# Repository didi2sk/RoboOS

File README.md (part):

# RoboOS

**English** | [Slovensky](README.sk.md)

A mini operating system for the Raspberry Pi that runs directly on the hardware, no Linux.
You control it with a **USB keyboard** or over a serial line (UART). Output goes to
HDMI and UART at the same time, and both inputs work together.

Current version: **0.150**

## Supported boards

One `kernel8.img` runs on every board with the 64-bit BCM2837 chip; the board is
detected at boot (shown under the logo and in the prompt, e.g. `robo@zero2`).

| Board | Notes |
|-------|-------|
| Raspberry Pi 3 Model B / B+ / A+ | tested on 3B |
| Raspberry Pi Zero 2 W | mini-HDMI; keyboard through an **OTG adapter** on the port marked `USB` (power goes to `PWR IN`); hot-plug works on that port too, with or without a USB hub |
| Raspberry Pi 2 Model B **v1.2** | v1.2 has the BCM2837 (printed on the board: "Raspberry Pi 2 Model B V1.2") |
| Compute Module 3 / 3+ | |

Not supported: Pi 1, Zero / Zero W, Pi 2 v1.1 (32-bit chips), Pi 4 and Pi 5 (different
peripherals, USB behind PCIe).

The ACT LED is on the firmware GPIO expander (3B, CM3), GPIO29 (3B+, 3A+, Zero 2 W - active low)
or GPIO47 (Pi 2 v1.2).

## Putting it on an SD card

1. Format the SD card as **FAT32** with an **MBR** partition table (any size).
2. Copy the whole contents of the `sd/` folder onto it:
   `bootcode.bin`, `start.elf`, `fixup.dat`, `config.txt`, `kernel8.img`,
   plus the folders `APPS` (example programs), `RUN` (autostart) and `FIRMWARE` (WiFi chip firmware).
3. Put the card in the Raspberry Pi and power it on.

## GPIO header (pinout)

*Picture: [Raspberry Pi documentation](https://www.raspberrypi.com/documentation/computers/raspberry-pi.html), © Raspberry Pi Ltd, [CC BY-SA 4.0](https://creativecommons.org/licenses/by-sa/4.0/).*
Odd pins (1, 3, ... 39) = the inner row, even pins (2, 4, ... 40) = the row at the board's edge. The numbers in
RoboOS commands are always **GPIO numbers**, not header pins.

What RoboOS uses by default:

| GPIO (header pin) | used for |
|---|---|
| 2, 3 (3, 5) | I2C: sensors, displays, RTC, FM radio, I2C keypad |
| 14, 15 (8, 10) | UART console (USB-TTL adapter) |
| 8-11 (24, 21, 19, 23) | SPI: RC522 card reader, Waveshare OLED HAT |
| 4 (7) | 1-Wire on the IoT shield (no driver yet) |
| 17, 27, 22, 5 (11, 13, 15, 29) | IoT shield inputs IN1-IN4 = alarm zones (`alarm shield`) |
| 24, 25, 12, 16 (18, 22, 32, 36) | IoT shield outputs / relays (24 = alarm siren) |
| 23 (16) | IoT shield LED (alarm LED) |
| 6 (31) | doorbell button (THT shield) |
| 11, GND, 0, 5, 6, 13, 19, 26 (23-37 inner row) | 4x4 keypad pushed straight on (`alarm keypad plug`) |
| 18, 19 (12, 35) | sound on the Zero 2 W (the Pi 3 uses its jack) |

## Programs and autostart

The SD card is also RoboOS's disk (FAT32 or FAT16, read and write).
RoboOS has its own SD driver (the firmware only loads `kernel8.img` and then steps aside).
If the card is not found, `sd init` shows which step failed and the controller registers.
Since 0.28 the card runs on the SDHOST controller (as in Linux), so that the second controller
(Arasan) is free for WiFi later; if SDHOST does not work, RoboOS uses the Arasan as before and the
boot screen shows a yellow `SDHOST:` line with the reason. `sd` shows which one is used,
`sd init sdhost` / `sd init emmc` try one of them.

- Everything in **`/RUN`** (`*.bin` and `*.bas`) starts automatically after boot,
  in alphabetical order. Press any key within 2 s to skip the autostart.
- `run <name>` starts a program from the current directory, `/RUN` or `/APPS`; the extension
  is optional.
- Moving around the card: `cd APPS`, `cd ..`, `cd /`, `pwd`; the prompt shows where you are
  (`robo@rpi3:/APPS$`). All commands and BASIC (`LOAD`, `SAVE`, `DIR`) take paths relative
  to the current directory. **Tab** completes file and directory names.
- `mkdir <dir>` makes a directory (8.3 name), `rm <file>` deletes a file, `rm <dir>` an empty
  directory. The firmware and kernel files in `/` are protected: deleting them needs `rm -f`.
- **Ctrl+C** stops a running program and returns to the shell.

### BASIC - write programs directly on the RPi

```
robo@rpi3:~$ basic
] 10 PINMODE 17, OUT
] 20 GPIO 17, HIGH : WAIT 500
] 30 GPIO 17, LOW : WAIT 500
] 40 GOTO 20
] RUN                      (Ctrl+C stops it)
] SAVE "/RUN/blink"        (saved as /RUN/blink.bas -> starts after every boot)
] BYE
```

- Commands: `RUN`, `LIST [a-b]`, `NEW`, `SAVE "name"`, `LOAD "name"`, `DIR [path]`, `HELP`, `BYE`;
  `MKDIR "dir"`, `RMDIR "dir"`, `KILL "file"` work in programs too.
  Typing a line number alone deletes that line.
- Statements: `PRINT`/`?`, `INPUT`, `LET`, `IF..THEN..ELSE`, `GOTO`, `GOSUB`/`RETURN`,
  `FOR..TO..STEP`/`NEXT`, `DIM`, `END`, `REM`/`'`, `CLS`, `RANDOMIZE`; separate statements with `:`.
- GPIO: `PINMODE pin, OUT|IN|PULLUP|PULLDOWN`, `GPIO pin, HIGH|LOW`, `GPIO(pin)`, `LED ON|OFF`, `WAIT ms`.
- Pictures: `IMAGE "file", x, y [, w, h]` (see the pictures section).
- Video: `VIDEO "file.mpg"` (see the video section).
- Sound: `SOUND Hz, ms`, `PLAY "notes"`, `VOLUME 0-100`, `PLAYWAV "file.wav"` (see the sound section).
- Network: `NETSEND`, `NETOK`, `NETAVAIL`, `NETRECV`; TCP/UDP: `TCPCONNECT`, `TCPLISTEN`,
  `TCPACCEPT`, `UDPOPEN`, `SOCKPRINT`, `UDPSEND`, `SOCKAVAIL`, `SOCKGET`, `SOCKNUM`, `SOCKCLOSE`
  (see the network sections).
- Functions: `ABS()`, `RND(n)`, `MIN(a,b)`, `MAX(a,b)`, `MILLIS`, `MICROS`, `INKEY`, `TEMP`, `CHR$()` (in PRINT).
- Integers only (64-bit). Keywords must be separated by spaces. `.bas` files are plain text,
  so you can also write them on a PC.
- File names when saving: 8.3 (max 8 characters + extension).

Examples on the card: `APPS/blink.bas`, `APPS/button.bas`, `APPS/knight.bas`,
`APPS/ledsrv.bas` (LED controlled over TCP), `APPS/udptemp.bas` (temperature over UDP),
`APPS/sound.bas` (tones and a tune).

### Text editor

`edit <file>` opens a full-screen editor, so `.bas` and text files can be written and
changed right on the RPi (`edit /RUN/blink.bas`, then `run blink`).

| Key | Action |
|-----|--------|
| arrows, Home, End, Page Up, Page Down | move the cursor |
| Backspace, Delete, Enter, Tab | edit (Tab inserts spaces) |
| Ctrl+S | save |
| Ctrl+Q | quit (asks if there are unsaved changes) |
| Ctrl+K / Ctrl+U | cut the current line / paste it above the cursor line |
| Ctrl+L | redraw the screen |

- Files up to 1 MB. New files are saved with 8.3 names (max 8 characters + extension);
  a file with a long name can be viewed but not saved.
- Line ends are kept as they were (CR LF or LF); new files use CR LF.
- On a UART terminal the editor uses the HDMI text size (128x48), so make the terminal
  window at least that big; without HDMI it uses 80x24.

### C programs (SDK)

The `sdk/` folder builds programs in C with an Arduino-style API:

```c
#include "robos.h"

void setup(void) { pinMode(17, OUTPUT); }

void loop(void)
{
    digitalWrite(17, HIGH); delay(500);
    digitalWrite(17, LOW);  delay(500);
}
```

`cd sdk && make` turns every `examples/*.c` into `bin/*.bin`; copy those to the card
(`/RUN` for autostart). API: `pinMode`, `digitalWrite`, `digitalRead`, `delay`,
`delayMicroseconds`, `millis`, `micros`, `print`, `println`, `printf`, `getKey`,
`clearScreen`, `textColor`, `actLed`, `cpuTemperature`, `stopRequested`, `exit`,
`netSend`, `netReceive`, `netName`, and TCP/UDP: `tcpConnect`, `tcpListen`, `tcpAccept`,
`udpOpen`, `sockWrite`, `sockPrint`, `sockRead`, `sockAvailable`, `udpSendTo`,
`udpReceiveFrom`, `sockClose`, `sockError`, `ipAddress`, and sound: `tone(hz, ms)`, `noTone`,
`playNotes`, `soundVolume`, `playWav`, pictures: `drawImage(path, x, y, w, h)`, `imageError`, and
video: `playVideo(path)`, `videoError`, files: `readFile`, `writeFile`
(see `sdk/robos.h`). A program can use `setup()` + `loop()` or `main()`.
Examples: `hello`, `blink`, `button`, `knight`, `chat`, `tcpserv` (TCP server), `udpecho` (UDP),
`music` (a tune and a siren), `alarm` (see below).

### Demo: alarm (`alarm`)

Since 0.120 the alarm is also in the kernel (the `alarm` command, web page, Home Assistant - see
"Burglar alarm in the kernel"); this program stays as a programming example.
`run alarm` starts a small burglar alarm (`sdk/examples/alarm.c`); copy it to `/RUN` to start it
at boot. Its settings are in `/ALARM.TXT` (made with defaults on the first start):

```
code 1234                    # the PIN that arms and disarms
exit 20                      # seconds to leave after arming
entry 15                     # seconds to disarm after a "delay" zone opens
siren 180                    # seconds of siren (0 = until disarmed)
siren_pin 24                 # output: siren / relay (HIGH = on)
armed_pin 23                 # output: LED - on = armed, blinks = exit / entry time, fast = alarm
sound on                     # countdown beeps, siren tone, voice on the audio jack
volume 80
voice /ALARM                 # folder with voice WAV files ("none" = tones only)
port 8080                    # TCP port for JSON (0 = off)
zone 17 delay nc Front door  # zone <gpio> <instant|delay|24h> <nc|no> <name>
zone 27 instant nc Window
zone 22 instant no PIR hall
zone 5 24h nc Tamper
```

- **Inputs** use the internal pull-up: wire each contact between the GPIO and GND. `nc` = normally
  closed (door contact: open = alarm), `no` = normally open (PIR relay, panic button: closed = alarm).
  `instant` = alarm at once while armed, `delay` = starts the entry time (the way in, ignored
  during the exit time), `24h` = alarm at any time, also disarmed (tamper, panic). It refuses to
  arm while an instant / 24h zone is open.
- **Serial port / keyboard**: `arm 1234`, `disarm 1234`, `status` (the code is shown as `*`).
  Every event is printed as `[ALARM hh:mm:ss] ...` on the serial port and the screen.
- **JSON** on the TCP port: one line with `nc <board> 8080`, or HTTP
  (`curl -d "{\"cmd\":\"disarm\",\"code\":\"1234\"}" http://<board>:8080/`; GET = status):
  `{"cmd":"arm","code":"1234"}`, `{"cmd":"disarm","code":"1234"}`, `{"cmd":"status"}`.
  The answer has the state, the siren, the seconds left, the cause and every zone.
- **Sound**: a beep every second of the exit / entry time, the last 10 seconds spoken, the
  siren as a rising and falling tone, and spoken events. The card has Slovak voice files in
  `/ALARM` (`ARMING`, `ARMED`, `ENTRY`, `ALARM`, `DISARMED`, `WRONG`, `NOARM`, `1`-`10` `.WAV`),
  made by `tools/mkvoice.sh sk` with espeak-ng (`tools/mkvoice.sh en` for English) - replace
  them with your own recordings. A voice file plays to its end before the alarm goes on.
- Five wrong codes block the code for 60 s. It is a demo: Ctrl+C on the board ends it.

Programs can read and write files since API version 8: `readFile(path, buf, max)`,
`writeFile(path, data, len)`.

Programs are loaded at 0x01000000 (max 16 MB). A crash inside a program prints the
exception and returns to the shell.

**GPIO is 3.3 V** (not 5 V like an Arduino Uno), max about 16 mA per pin.
Use a 220-330 Ω resistor for LEDs and a transistor/module for relays and motors.

## Pictures

RoboOS shows JPEG (also progressive), PNG (with transparency), BMP and GIF (the first frame)
on the HDMI screen; a big picture is scaled down to fit, keeping its shape.

- `view <picture>` shows it full screen; **Left/Right** (or Space) go to the previous / next
  picture in the same directory, **Q** or Enter returns to the text screen as it was.
  `view <dir>` starts with the first picture there.
- **Boot picture**: a file `/SPLASH.PNG` (or `/SPLASH.JPG`, `/SPLASH.BMP`) is shown while
  RoboOS starts; the boot messages appear behind it and show up after at least 2.5 s
  (a key ends it sooner). The card comes with a RoboOS picture - put your own there
  (best 1024x768), or delete it to boot straight to the text.
- BASIC: `IMAGE "photo.jpg", x, y` draws a picture at x, y (pixels; 1024x768 unless `screen` changed it);
  `IMAGE "photo.jpg", x, y, w, h` fits it into a w x h box. C: `drawImage(path, x, y, w, h)`.
- Pictures are decoded in memory: a 12-megapixel phone photo takes a few seconds.

## Screen resolution

The text screen starts at 1024x768. `screen 1280x720` (any size from 320x200 to 2048x1280)
switches right away and is saved in `/SCREEN.TXT`, so the next boot uses it too;
`screen auto` uses the monitor's own resolution (what the firmware found on HDMI),
`screen` alone shows the current size and the monitor's. If the picture stays black,
delete `/SCREEN.TXT` on a PC (or put `1024x768` in it).

RoboOS asks the graphics chip for **two screen pages**: the text is on the first one, a
video is drawn on the hidden one and then shown in one step (page flip), so it does not tear.

## Video

`video <file.mpg>` plays a video full screen with sound (jack, GPIO18/19 or an I2S DAC -
`sound out` chooses). **Q** or Enter stops it, **Space** pauses, **Left/Right** jump 10 s
back / forward; the shell then prints how many frames were shown and the frame rate.

The format is **MPEG-1 video with MP2 sound** (`.mpg`, as on a Video CD): free to use, the
patents have expired long ago, and the decoder (pl_mpeg) is small enough to run directly on
the board. MP4 (H.264 / AAC) is licensed and needs the GPU's hardware decoder, whose
interface is closed, so RoboOS does not play it. Convert any video on a PC with ffmpeg:

```
ffmpeg -i film.mp4 -vf scale=640:-2 -c:v mpeg1video -q:v 4 -c:a mp2 -b:a 192k -f mpeg FILM.MPG
```

- 640x360 or 640x480 at 25/30 fps is a good size for a Pi 3; the picture is scaled to
  fit the screen (at most 2x bigger), keeping its shape. `-q:v` 2 (best) .. 10 (smallest).
- The work is split between the cores: core 0 reads the card and decodes, **cores 2 and 3**
  convert the colours (YCbCr to RGB) and scale the previous frame at the same time, core 1
  keeps USB and the network running. If the board cannot keep up, frames are skipped
  (the sound never is).
- BASIC: `VIDEO "film.mpg"`; C: `playVideo(path)` (API version 7, `videoError()`).

## Network: messages between RoboOS boards

The Pi 3B (LAN9514) and the Pi 3B+ (LAN7515) have an Ethernet chip that is a USB device
behind the onboard hub; RoboOS has a driver for both (both work: DHCP, NTP). The 3B links at 100 Mbit, the 3B+
at 1000 Mbit (`net speed 100` limits it; over USB 2.0 the chip moves at most ~300 Mbit). Plug the
boards into the same switch or router and they can send each other short text messages.
The protocol is RoboOS's own, on raw Ethernet frames (EtherType `88b5`), so a PC does
not understand it. For talking to PCs and the internet there is TCP/IP (next section).

```
robo@rpi3:~$ net who
  rpi3-1c2d        b8:27:eb:11:1c:2d  seen 0 s ago
robo@rpi3:~$ net send rpi3-1c2d hello
delivered
```

- Every board has a name: by default `rpi3-` + the end of its MAC address.
  `net name <new>` changes it and saves it to `/NAME.TXT` on the SD card.
- `net who` asks who is on the network. `net send <name> <text>` sends a message and
  waits for the confirmation (3 tries); `net send all <text>` goes to everybody, unconfirmed.
- A message that arrives while you are at the shell prompt is printed as `[NET] name: text`.
  While a program runs, messages wait in an inbox (the last 8) for the program.
- `net` shows the name, chip, MAC address, link state and counters. `net test [seconds]`
  lists all frames on the wire, `net loop on` makes sent messages come back to the same
  board (try things with one board, or in QEMU).
- BASIC: `NETSEND "name", 42` or `NETSEND "ALL", "text"`; `NETOK` tells if the last send
  went through; `NETAVAIL` is the number of waiting messages and `NETRECV` returns the
  oldest one as a number. Example: one board sends its button, the other lights an LED:

  ```
  10 PINMODE 27, PULLUP : REM board A        10 PINMODE 17, OUT : REM board B
  20 NETSEND "ALL", GPIO(27) : WAIT 100      20 IF NETAVAIL THEN GPIO 17, NETRECV = 0
  30 GOTO 20                                 30 GOTO 20
  ```
- C programs: `netSend(to, text)`, `netReceive(from, text, max)`, `netName()`;
  see `sdk/examples/chat.c` (`run chat` = a chat between the boards).

Not available on the Zero 2 W and 3A+ (no Ethernet). The 3B and 3B+ can talk to each other.

## Network: TCP/IP

RoboOS uses [lwIP](https://savannah.nongnu.org/projects/lwip/) 2.2.1 (in `lwip/`,
BSD license), a small TCP/IP stack written for systems without an operating system.
After boot the board asks the router for an address (DHCP) and sends its name with it,
so the router's list of devices shows it under its RoboOS name. When the address
arrives, `[NET] IP address ...` appears at the prompt.

```
robo@rpi3:~$ ip
host:    rpi3-9a4f
link:    up
address: 192.168.1.37 / 255.255.255.0  (DHCP)
gateway: 192.168.1.1
dns:     192.168.1.1
robo@rpi3:~$ ping 192.168.1.1
reply from 192.168.1.1: seq=1 ttl=64 time=0.9 ms
```

- `ip` shows the address; `ip set <address> [mask] [gateway]` sets a fixed address,
  `ip dhcp` goes back to DHCP. The choice is saved in `/IP.TXT` on the SD card.
- `ping <address or name> [count]` - names are looked up with DNS.
- `ip` also counts the frames: `in` (ARP, IPv4, other, VLAN-tagged) and `out` (errors) -
  if `in` stays near 0, nothing reaches the board (cable, switch, router). Frames with a
  VLAN tag (802.1Q, also the "priority only" tag some routers add) have the tag removed.
- `http on` starts a small web page with the board's name, version, uptime and CPU
  temperature: open `http://<address>/` in a browser. `http off` stops it. The choice is
  saved in `/HTTP.TXT`, so the page (and the API below) comes back after a reboot.
- IPv4 only.

### WiFi (being built)

The WiFi chip (CYW43438 on the Pi 3B, CYW43436 on the Zero 2 W, CYW43455 on the Pi 3B+) hangs on
SDIO. RoboOS starts it, looks for networks and joins one (WPA2-PSK, or open):

```
wifi scan                     load the firmware into the chip and list the networks around
wifi join MyNet password      join (saved in /WIFI.TXT: the board joins by itself after a reboot)
wifi join "My Net" password   a name with spaces
wifi                          chip, firmware, MAC address, network, signal
wifi band 2|5|auto            only 2.4 GHz / only 5 GHz / both (Pi 3B+ only - the 3B and Zero 2 W have 2.4 GHz; saved; a network with both bands:
                              the firmware picks one, 'wifi' shows the channel it got)
wifi leave                    disconnect (and stop re-joining);  wifi forget  also deletes /WIFI.TXT
```

The chip's own firmware does the WPA2 handshake. One IP interface carries everything (DHCP,
web, API, HTTPS, NTP, programs): **Ethernet when its cable is in, otherwise WiFi** - pulling the
cable switches to WiFi (`[NET] now on WiFi`, a new address by DHCP). `ip` shows which one is used.
The Zero 2 W has no Ethernet, so WiFi is its network.

The chip needs its firmware on the card in `/FIRMWARE` - it is in `sd/FIRMWARE`, so copying
`sd/` is enough (`tools/getwifi.sh` downloads a fresh copy): `brcmfmac43430-sdio.bin` + `.txt` +
`.clm_blob` (Pi 3B; the newer firmware does not switch the radio on without the `.clm_blob`), `brcmfmac43436-sdio.bin` + `.txt` + `.clm_blob` (Zero 2 W), `brcmfmac43455-sdio.bin` +
`.txt` + `.clm_blob` (Pi 3B+). These files are not RoboOS: unmodified copies from Raspberry Pi's
firmware-nonfree package under the Cypress / Synaptics licenses, which allow redistributing them
for use with their chips - see `sd/FIRMWARE/README.txt` and the `LICENCE.*` files next to them.
WiFi needs the SD card on SDHOST (see the SD card section). Scan and join work on the Pi 3B;
the scan works on the Pi 3B+ (2.4 and 5 GHz). The Pi 3B+ firmware has no built-in WPA supplicant,
so since 0.36 RoboOS does the WPA2-PSK handshake itself (`src/wpa.c`: PBKDF2, the 4-way and group
key handshakes, AES key unwrap; checked on the PC against the IEEE 802.11 test vectors and a Python
access point, `tools/test_wpa.py`) - `wifi join` then says "RoboOS does the WPA2 handshake" (just information).
If the join fails (at boot, a lost link, a rebooted router), the board tries again by itself: after 20 s,
then every minute (`[NET] WiFi: joining <net> again`), until `wifi leave`. This **works on the Pi 3B+** (joined, DHCP and ping over WiFi with the cable out). WPA3-only networks (SAE) are not
supported (WPA2/WPA3 mixed are fine).
**The Zero 2 W works too** (boot, USB keyboard through OTG, WiFi).

### Bluetooth (BLE: sensors, phone)

The WiFi chip is a Bluetooth chip too. It is switched on only when you ask:

```
bt on            switch on: listens to the devices around and can be found by a phone
bt scan          what is around (bt scan 20 = listen 20 s)
bt sensors       Bluetooth thermometers as JSON
bt pair          pair a Bluetooth keyboard (classic BT; bt pair aa:bb:cc:dd:ee:ff = that one)
bt forget        forget the paired keyboard
bt               status (connected phone, devices, thermometers)
bt off           switch off
bt auto on|off   switch on at boot (/BT.TXT)
```

**Sensors.** Xiaomi LYWSD03MMC thermometers with the free ATC / pvvx firmware (service data
0x181A) are read all the time while Bluetooth is on: `bt sensors`, `GET /api/ble`
and MQTT `roboos/<name>/ble/<mac>` = `{"temp":21.53,"hum":45.12,"batt":87,"rssi":-63,"name":"ATC_112233"}`
(at most every 30 s), Home Assistant finds them by itself (temperature, humidity, battery).
`bt scan` also shows names and makers of everything else (phones, TVs, headphones).
Since 0.43 it also searches for classic Bluetooth devices (marked `BR`) and marks keyboards and mice:
`[keyboard, BLE]` or `[keyboard, classic BT]` - so you can see which kind your keyboard is
(cheap ones are often classic Bluetooth 3.0, which needs a different driver than BLE ones).

**Phone.** The board shows up as its name (`rpi3-...`) with the Nordic UART Service. Connect with
a terminal app - Android: *Serial Bluetooth Terminal* (Devices -> Bluetooth LE), iPhone / Android:
*nRF Toolbox* (UART) or *Bluefruit Connect* (UART) - and type:

```
help                          the commands
status                        name, version, uptime, address, time
sensors                       CPU, BME280, ADS1115 and the Bluetooth thermometers
gpio 17                       read a pin;  gpio 17 1 / gpio 17 0 / gpio 17 toggle = set it
login robo MyPassword1        needed when users exist ('users add'); a "view" user only reads
```

There is no pairing yet: the link is not encrypted, use it nearby (a password typed there
crosses the air readable). While Bluetooth is on, the UART console runs on the mini UART - same
pins 8/10, same 115200; `bt off` gives it back. Scanning works on the Pi 3B (19 devices on the first
try) and the Zero 2 W (12 devices); the phone part is tested in QEMU (`tools/qemu_bt_test.py` plays the controller and a phone).

**Keyboard (0.44, classic Bluetooth).** Put the keyboard into pairing mode (usually hold Connect or
Fn+C until its LED blinks) and type `bt pair`. RoboOS finds it, connects and shows a number:
`on the keyboard type 123456 and press Enter` - type it **on the Bluetooth keyboard**. Then it
types into the shell like a USB keyboard (US layout, autorepeat). The link key is saved in
`/BTKEYS.TXT`: after a reboot (with `bt auto on`) or when the keyboard slept, press a key and it
connects by itself. `bt` shows the state, `bt forget` deletes the key. BLE keyboards are not supported
yet. The 3B+ chip comes with a placeholder Bluetooth address (43:45:c0:00:1f:ac, the same on every
board); since 0.44 RoboOS gives it its own (b8:27:eb + serial number, like Raspberry Pi OS).
**Works on the Pi 3B+** with a cheap classic BT keyboard (pairing, typing, reconnect after a reboot);
0.45 lets the keyboard authenticate by itself when it calls (0.44 crossed it: error 0x05, one retry).
0.45 also loads the Bluetooth firmware at 921600 baud (8x faster: `bt auto on` no longer adds ~6 s to
the boot) and leaves the WiFi join at boot to the I/O core, so the router's WPA handshake is answered
at once (before, the 3B+ often joined only on the retry 20 s later).
0.46: Bluetooth listens in the background only 10 % of the time (30 ms every 300 ms, `bt scan` 50 %) - WiFi
and Bluetooth share one radio, and the 50 % scan made the WPA handshake fail until the 3rd try on the 3B+;
WiFi retries say why the last try failed. 0.49: a retry never cuts short a try that is still
associating or doing the WPA handshake (0.46 retried after 10 s and so joined only on the 4th try): after an
error 2 s, otherwise 20 s; the time a try took is printed (`connected to ... (N s)`). 0.50: on the 3B+ (RoboOS does the WPA handshake) the firmware's
own WPA status is ignored - 0.49 took it for a failure and restarted joins in the middle of the handshake (10 tries). 0.51: `wifi` lists the last 10 joins with the time of
each step (network found, link, WPA msg1/msg3, keys, lost + reason) - one photo shows where a join stops. 0.52: the owner's router answered
the quick retries with deauth reason 2 ("previous authentication no longer valid") 20 times: now every retry first
leaves cleanly (disassociate, 0.3 s) and a refused try is retried after 15 s, not 2 s. On the Pi 3B+ WiFi now joins on the first try within a second.
0.53: with `bt auto on` and WiFi set up, Bluetooth starts only after WiFi has joined (at most 15 s later) -
both share one radio, and the Bluetooth start made the boot-time WiFi join take 20 s.
0.54: `history` lists the last 30 shell commands (was 10), `!N` / `!!` run one again, `history clear`; the history is kept
in `/HISTORY.TXT` on the card, so it survives a reboot. WiFi: a refused FIRST try after a boot is retried after 3 s (not 20 s), and so is a first
try whose WPA handshake stalls (msg2 sent, no msg3 within 5 s) - the owner's photo: at boot the router never answered our msg2 and
dropped the board after 18 s, the second try then joined in 3 s.
0.55: I2C displays - SSD1306 / SH1106 OLED and 16x2 / 20x4 LCDs with a PCF8574 backpack, found at boot, status screen
(name, IP, time), `display`, BASIC `DISPLAY`, C API 11 (see "I2C display").
0.56: `ai` - questions to Claude with your own API key (see "AI"); shell lines up to 255 characters; more root CAs
for HTTPS (DigiCert G5, SSL.com, Certainly, Microsoft, IdenTrust).
0.57: OLED displays that never acknowledge on I2C (2.42" SSD1309 boards with the D2 jumper open - they worked on an ESP,
whose software I2C ignores ACK): `display type ssd1306` uses them anyway, written by bit-banged I2C on GPIO2/3.
Also OLED controllers that answer writes but not reads (SSD1309) are now found: `i2c scan` and the display search try
0x3C/0x3D with a write too.
0.58: display fonts (small 21 x 8 / normal / big), `display console on` (a copy of the terminal), text over the network
(`/api/display`, MQTT `set/display`). The 2.42" OLED works on the 3B+ (owner: IP and time shown).
0.59: `display font tiny` = 32 x 10 characters (X11 4x6, public domain); the OLED is drawn into a picture in memory and
only the changed 8-pixel stripes are sent. Rows 1-10 in BASIC, the API and MQTT.
0.60: `display time` = a big digital clock (with the date on 128x64), `display info` = the status screen;
`display console off` goes back to the status screen (in 0.59 it left the display empty). The mode is saved.
0.61: the clock in thin digits (DejaVu Sans, `tools/mkclock.py`) instead of the blocky 3x font, the seconds smaller
right beside HH:MM, the date in the 8x16 font below.
0.62: `font tiny` is now the clearer X11 5x8 (25 x 8); the cramped 4x6 (32 x 10) is `font micro`.
0.63: a plain API key typed into `/AI.TXT` on a PC (`key sk-ant-...`) is accepted and scrambled at the first `ai`.
0.64: also just the bare key in `/AI.TXT`, or `API_KEY="sk-ant-..."` - any line with `sk-ant-`.
0.65: `ai` prints every step (connecting, TLS handshake, sending, waiting, reading, with ms) - the owner saw it
stop after "asking ..." with no clue where.
0.66: more for the hang hunt: the answer line shows the HTTP status, length and chunked; while waiting, every 5 s
"still waiting: N bytes in so far, core 1: <what it does> (loops)".
0.67: FIX the `ai` freeze: after a chunked answer (the API answered HTTP 429) BearSSL's polite TLS close
(`br_sslio_close`) spun forever - reproduced in QEMU; the HTTPS client now just closes the TCP connection.
A 429 now hints at the rate / spend limit and the credit.
0.68: FIX `i2c scan` "finding" 0x3c / 0x3d with nothing connected (the write probe for OLEDs): a late no-ACK
is caught, and write probes are trusted only if the reserved address 0x7c does NOT answer. `i2c scan` also warns
when SDA / SCL are low while idle (short, swapped wires, an unpowered module).
0.69: still one phantom 0x3c on the owner's empty bus -> the write probe must answer 3 times in a row, `i2c scan`
marks such finds "[answers writes only]"; `i2c probe <addr>` shows the raw controller status + time of reads and
writes; `i2c speed <kHz>` (10-400, until reboot) - LCD backpacks (PCF8574) are rated for 100 kHz at most.
0.70: I2C bus clear - the owner's LCD backpack held SDA low ("SDA LOW" in `i2c scan`, nothing found) until a
failed transfer clocked it free; now at start-up, before `i2c scan` and after a timeout RoboOS sends up to 9 clock
pulses + a STOP whenever SDA is stuck low (`i2c scan` says so).
0.71: FM radio - `radio` for an RDA5807M module (tune, seek, scan, volume, RDS name + text, `display radio`,
/api/radio, MQTT set/radio); an MPU-6050 on 0x68 is no longer taken for the DS3231 clock (WHO_AM_I check).
0.72: Waveshare 1.3" OLED HAT (SH1106 on SPI0 + 3 keys + joystick) as a radio panel: `display hat`, `display keys`;
new SPI0 driver `src/spi.c`.
0.73: BMP180 (BMP085) pressure + temperature sensor at 0x77 in `sensors`, MQTT, the API and BASIC `SENSOR()`.
0.74: DCF77 radio clock receiver on a GPIO pin (`dcf`): the time without a network.
0.75: `dcf on` / `dcf off` (the pin is kept; with `dcf pon` the receiver is powered down too).
0.76: `dcf` shows how long each level lasted (a table + the last 12 periods) to tell a real signal from noise.
0.77: noise-tolerant DCF77 decoder: it locks onto the 1 s rhythm and judges each second as a whole (spikes no
longer break pulses); two good minutes that fit together set the clock even with bad minutes in between.
0.78: DCF77 with a weak / noisy signal: the minute start is found by itself and the bits are summed over
several minutes (hour and date stay, the minute goes +1), so the time comes even when every minute has errors.
0.79: AHT20 / AHT10 humidity + temperature sensor at 0x38 (e.g. the AHT20 + BMP280 board) in `sensors`, MQTT, API, BASIC.
0.80: offline voice commands with the DFRobot DF2301Q module (`voice`): a heard phrase runs a shell command.
0.81: I2C fix - after an address that did not answer, the next transfer failed (the controller was still
sending the STOP); `i2c scan` and the sensor search at boot missed devices that `i2c probe` saw.
0.82: sensors on the display (`display sensors`, also under KEY1 on the HAT), a CSV log (`sensors log 5` ->
/LOG/YYYYMMDD.CSV) and `GET /api/sensors` (JSON).
0.83: MPU-6050 / GY-521 (`motion`): tilt (spirit level), acceleration, rotation, shake detection; display, MQTT, API, BASIC.
0.84: MPU-6050 wake-up fixed (a GY-521 stayed asleep and gave all 0, which also counted fake shakes).
0.85: `motion` runs live on the whole screen until a key (spirit-level bars for pitch / roll); `motion once` prints once.
0.86: MPU-6050 on its internal oscillator (a GY-521 woke up but measured nothing with the gyro clock).
0.87: AMG8833 Grid-EYE thermal camera (`thermal`): live heat map on HDMI, person detection (MQTT), display, API, BASIC.
0.88: camera on the CSI ribbon, step 1 (`cam`): powers the camera and finds the sensor (OV5647 / IMX219).
0.89: camera step 2: `cam live` / `cam snap` / `cam bars` - the first picture from an OV5647 on HDMI (640x480).
0.90: `cam live` / `bars` print every start-up step (`cam 1` ... `cam 9`) - the board froze on 0.89, the last line shows where (`cam trace off` hides them).
0.91: while waiting for the first frame the camera lanes and the sensor exposure are printed every 0.5 s; `cam clock cont|ncont` tries the other MIPI clock mode.
0.92: `cam dump` prints every camera receiver register while streaming; `tools/camdump.py` prints the same on a Linux Pi where the camera works, to compare.
0.93: the camera now runs like the Pi firmware does: sensor mode 1296x972 (2x2 binned) and lane clock gate 0x155; `cam mode 640` / `cam gate 0x15` switch back for tests.
0.94: the sensor gets exactly the register list the Pi firmware writes (1296x976, logged by raspiraw) - no line sync packets; `cam mode fw|1296|640`.
0.95: the sensor is set up and streaming BEFORE the camera receiver starts (like rsta2/libcamera); `cam order rx` = the old order.
0.96: fix: in the firmware mode the sensor stayed in "no frames" (0x4202) from the start-up and sent only its clock.
0.97: Bluetooth keeps calling the paired keyboard until it answers (every 8 s, then 20 s, after ~3 minutes every 60 s), also after it disconnects.
0.98: `cam sregs` prints every camera sensor register RoboOS sets while it streams; `tools/ov5647regs.sh` prints the same list under Linux, to compare.
0.99: camera fix: while waiting for frames RoboOS kept writing the receiver status back (also its "synchronised" bits) thousands of times per second; now only error bits are cleared. Defaults like Linux on the same board: 1296x972 mode, gate 0x15, receiver first.
0.100: in the 1296 mode the sensor gets exactly the values Linux leaves in it (manual exposure 0x57e, gain 0x40, frame length 0x602, mirror 0x3821 = 3, no AWB).
0.101: camera BUG FOUND: RoboOS powered the wrong camera receiver (firmware power domain 13 = UNICAM0; the camera connector uses UNICAM1 = 14), so the receiver never saw data. Fixed - **the camera works on the Pi 3B+** (owner).
0.102: camera colours: the pixel colour order follows the sensor mirroring (GBRG in the default 1296 mode, like Linux); `cam bayer bggr|gbrg|grbg|rggb` if the colours look wrong.
0.103: camera photos as JPEG (`cam snap [file]`, s / space in `cam live`; own encoder `src/jpeg.c`) + picture settings saved in /CAM.TXT: exposure, gain, ev, white balance, brightness, contrast, saturation, hue, gamma, flip, JPEG quality (`cam set`).
0.104: camera web page `/camera`: live preview + sliders for every setting + save photo; API `GET|POST /api/camera`, `GET /api/camera.jpg`; `cam test on` = test picture without a camera.
0.105: video doorbell (`doorbell`: GPIO button -> photo on the card + to Home Assistant over MQTT, gong / WAV, ring event) and door radar (photo when someone comes); MQTT camera, Take photo button, doorbell event, radar sensor via discovery; `cam send`.
0.106: IR light on a GPIO for the camera (`cam ir <pin>`, `cam ir_mode off|on|photo|auto`; auto = only in the dark), also on the /camera page.
0.107: HC-SR04 distance sensor for the door (`doorbell distance <trig> <echo> [cm]`): a photo only when someone is nearer than the limit (with a radar: both).
0.108: `microscope` - full-screen live camera with zoom 1-5x (sensor pixels), arrows, photo (space) and MJPEG AVI video (v).
0.109: microscope in full resolution and full screen: sensor mode 1920x1080 (`cam mode 1080` too), every screen pixel drawn from the sensor pixels on 3 cores, `f` = fill / fit, photos up to 1920x1080.
0.110: camera sharpness (slider + `cam sharpness`), less flicker: a frame being drawn is never overwritten by the next one, exposure in whole mains periods (`cam flicker 50|60|off`), calmer auto exposure and white balance.
0.111: microscope without smears in motion: drawn on the hidden screen page and shown whole (double buffering); `k` / `cam cores 1-3` = how many cores draw.
0.112: microscope zoom in finer steps up to 2.5x: 1, 1.2, 1.5, 1.8, 2, 2.2, 2.5 (`+` / `-`, keys 1-7).
0.113: with `cam flicker 50|60` the auto exposure never goes below one mains period (10 / 8.3 ms) - a bright scene lowers the gain instead (lamp blinking gone).
0.114: microscope: Enter stops a video instead of quitting (only `q` quits), saving shows progress (% , MB, seconds left).
0.115: camera noise reduction (`cam denoise on|off`, checkbox on the page, `d` in the microscope); microscope keys `,` `.` = sharpness.
0.116: every slider of the `/camera` page takes effect on the next frame, also while the microscope / `cam live` run (brightness, contrast, saturation, hue, gamma and a fixed exposure / gain did not).
0.119: date + time stamp in photos, videos and Home Assistant photos (`cam stamp on|off`, checkbox on the `/camera` page).
0.120: burglar alarm in the kernel (`alarm`, web page `/alarm`, Home Assistant alarm panel + zone sensors + events over MQTT): zones instant / delay / interior / 24h, away / home, siren relay + tone + voice, photos + video on an alarm, photo at entry, event log /ALARM.LOG, armed again after a power cut; `alarm shield` for the IoT shield pins.
0.121: alarm keypads and card readers: 4x3 / 4x4 keypad on GPIO or on a PCF8574 (I2C), RC522 RFID reader (SPI), Wiegand readers / keypads; `alarm card learn|add|del`, code + # on the keypad, display mode `alarm` (state, stars, seconds left).
0.122: kernel update from the web: page `/update` with "Check" and "Install" buttons (the board downloads from GitHub itself, backup KERNEL8.BAK, reboots, the page waits for it), `GET|POST /api/kernel`.
0.123: the SD card is tried up to 4 times at boot (the owner's 3B often needed `sd init` after a reboot); when a retry was needed the boot line says how the first try failed.
0.124: SD init no longer asks the card for 1.8 V signalling (S18R - the Pi 3 cannot do it; large SDXC cards may misbehave), and a boot retry powers the card off and on first. Settings like the web token and `http on` are read from the card at boot - when the card was not mounted they were missing.
0.125: the card heals itself: a failed block read / write re-initialises the card once and tries again, and if the card was not mounted at boot every file access tries to mount it again (at most every 2 s). `sd` shows how often that happened.
0.126: re-initialising the card never touches the WiFi pins / the Arasan controller any more (in 0.125 an automatic card re-init could cut off the WiFi); the boot tries the SDHOST controller 3 times before falling back to the Arasan.
0.127: the WiFi firmware files are read from the card into RAM before the WiFi chip starts (on a 3B with a Samsung 64 GB card the card failed while its reads alternated with the firmware upload).
0.128: new home page (`http://<board>/`): status tiles (uptime, time, CPU, network, address, alarm, API, HTTPS), cards for Alarm / Camera / Photos & videos / Files / Update / JSON API, and a Reboot button (token or admin login; the page reloads when the board is back).
0.129: `alarm keypad gpio` with no pins = a 4x4 membrane keypad straight on the header (GPIO 5 6 13 19 / 12 16 20 21 = pins 29 31 33 35 / 32 36 38 40), wiring table in the README.
0.130: `alarm keypad plug [reversed]` = the keypad's 8-pin connector pushed straight onto header pins 23-37 (no wiring; the wire on the GND pin is read the other way round, all 16 keys work); keypad lines may be `gnd` in `alarm keypad gpio`.
0.131: `alarm keypad shield` (keypad with the IoT shield: GPIO 13 19 26 21 / 20 7 18 + GND); pin clashes between the keypad / card reader and alarm zones or the doorbell button are shown (`!!`, `PIN TAKEN`) and such a zone is not watched.
0.132: `alarm keypad test` - live key / line levels for checking the keypad wiring.
0.133: while the alarm is on, the display's normal status screen shows the alarm (state, code as stars, seconds left) by itself; the console shows the typed code as stars (`[KEYPAD] code: ****`). A zone with nothing connected shows as open (e.g. the window of `alarm shield`) - remove unused zones (`alarm zone del 27`).
0.144: GSM / LTE modem for the alarm (SIM800L, A7670E, SIM7600E on pins 8/10): SMS on alarm / arm / disarm, calls in an alarm, SMS commands ARM / HOME / DISARM / STATUS from listed numbers (`modem`).
0.145: OLED module with a rotary knob + CONFIRM / BACK buttons as the alarm keypad (`alarm knob`): turn = digit, push = add it, BACK = delete, CONFIRM = send.
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
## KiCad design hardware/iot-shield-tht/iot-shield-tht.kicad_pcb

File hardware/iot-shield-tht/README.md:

# RoboOS IoT shield THT (v0.1 - first draft)

**English** | [Slovensky](README.sk.md)

The **hand-solderable** variant of the [IoT shield](../iot-shield/README.md): through-hole parts only, so it can be
built at home with an ordinary soldering iron. Same GPIOs as the SMD shield, so the same RoboOS setup
(`alarm`, MQTT, BASIC, the JSON API) works on both.

**Status: drawn and routed (Freerouting, 300 passes), not manufactured, not tested.** KiCad DRC: every net
connected, no clearance errors (only silkscreen warnings). Check everything before ordering.

| top | bottom (seen from below) |
|---|---|
|  |  |

Schematic: [iot-shield-tht-schematic.pdf](iot-shield-tht-schematic.pdf) (KiCad 7: `iot-shield-tht.kicad_sch`,
`iot-shield-tht.kicad_pcb`). Shopping list: [parts.csv](parts.csv).

## Size and mounting

85 x 56.5 mm (the size of a Pi 3): the HAT outline plus 20 mm that hang over the Pi's **SD card end**
(no connectors there). Mounting holes:

- H1-H4: Raspberry Pi 3 / 4 pattern, 58 x 49 mm
- H1, H2, H5, H6: Raspberry Pi **Zero / Zero 2 W** pattern, 58 x 23 mm

The 40-pin socket J1 (2x20 female, 8.5 mm) goes on the **bottom** side, everything else on top.
Cut the leads short on the bottom (the Pi's HDMI and audio jack sit under the board, 11 mm spacers).

## What is on it

| Block | Parts | RoboOS |
|---|---|---|
| Power 12-24 V | terminal J2, PTC fuse 2 A (RXEF200), 1N5822 reverse diode, TVS P6KE30CA, 5 V 2 A switching module R-78B5.0-2.0 (or TRACO TSR 2-2450, Mornsun K7805-2000R3 - same pins) to header pins 2+4 | - |
| 4 isolated inputs | J3 IN1-IN4 + COM, PC817 (DIP-4), 3.3 k, 1N4148 (5-24 V, ~7 mA at 24 V) | GPIO17, 27, 22, 5 - **low** = voltage on the input |
| 2 relays | K1/K2 SRD-05VDC-SL-C, BC337 drivers, 1N4148; contacts on J8/J9 (NO COM NC, pin 1 at the bottom) | GPIO24 (K1), GPIO25 (K2) - high = on |
| 2 MOSFET outputs | J4 OUT3 OUT4 V+, IRLZ44N (logic level) low side, 1N5819 flyback diodes | GPIO12 (PWM), GPIO16 - high = on |
| Analog | J5: 3V3, A0-A3, GND -> 1 k -> socket J11 for the common **ADS1115 module** (0x48) | `sensors`, MQTT `a0`-`a3`, BASIC `SENSOR(4..7)` |
| Clock | socket J10 for the small **DS3231 "RTC for Raspberry Pi" module** (0x68, CR1220 on the module) | the time at boot without a network |
| Button | SW1 6x6 mm, 10 k pull-up + 100 n | GPIO6 - **low** = pressed |
| LEDs | red D3 = 5 V (power), green D4 = GPIO23 (status) | `gpio 23 hi` |

## Things to know

- Relay contacts: **low voltage only** (max 24 V, 5 A) - the board has no 230 V creepage distances.
- 5 V reaches the Pi through header pins 2 and 4. **Do not plug the Pi's USB power in at the same time.**
- Input range 12-24 V, absolute max about 28 V (TVS standoff 25.6 V, R-78B 32 V).
- The polyfuse (2 A) covers the Pi, the relays and the MOSFET loads together.
- Analog inputs: 0-3.3 V only.
- Modules: the ADS1115 module sits **over the inputs** (only low parts there), the DS3231 module bottom right.
  The ADS1115 module's ADDR pin is tied to GND (address 0x48).
- The analog filter capacitors, relay LEDs and the separate 100 n caps of the SMD shield were left out to make room.

## Routing and rebuilding

Same tools as the SMD shield: `circuit.py` (parts + nets) -> `gen_sch.py` (schematic) -> `check_net.py`
(netlist == circuit.py) -> `gen_pcb.py` (placement from `place.py`) -> `route.py` (Freerouting 1.9.0 under
`xvfb-run`, own SES reader, GND planes) -> `bom.py` (parts.csv).

```
./make.sh /path/to/freerouting.jar 150     # everything, routed
```

Ordering the bare board: `iot-shield-tht-gerbers.zip` (Gerbers + drill), any PCB maker, 2 layers, 1.6 mm.

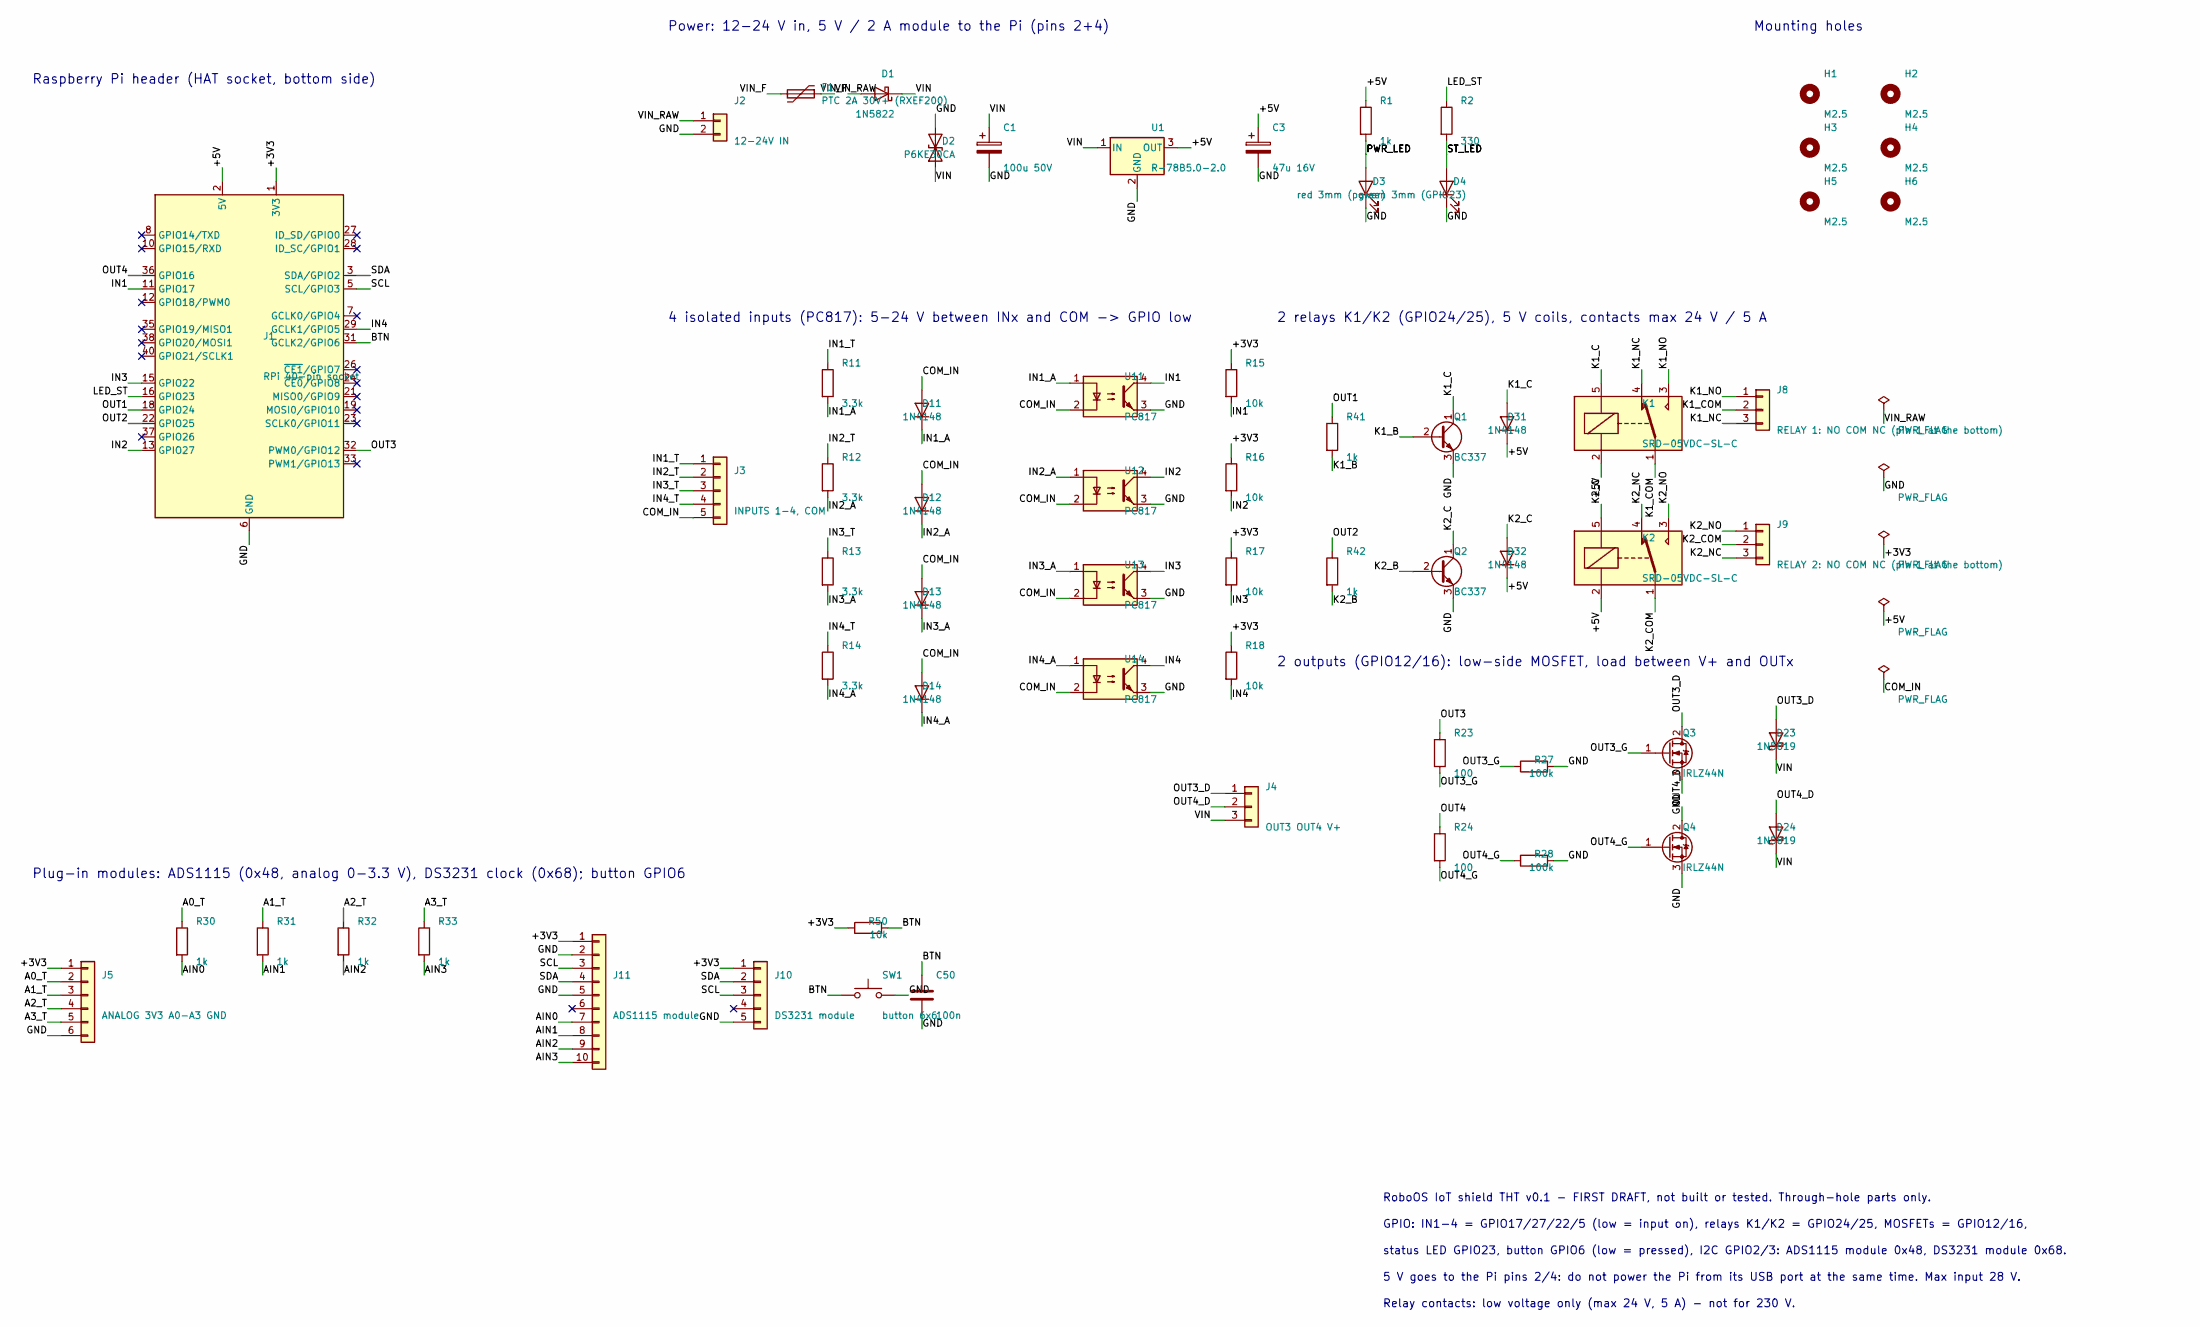
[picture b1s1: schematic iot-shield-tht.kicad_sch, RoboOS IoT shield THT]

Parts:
C1: 100u 50V; CP_Radial_D8.0mm_P3.50mm
C3: 47u 16V; CP_Radial_D5.0mm_P2.00mm
C50: 100n; C_Disc_D3.0mm_W1.6mm_P2.50mm
D1: 1N5822; D_DO-201AD_P5.08mm_Vertical_KathodeUp
D2: P6KE30CA; D_DO-15_P3.81mm_Vertical_KathodeUp
D3: red 3mm (power); LED_D3.0mm
D4: green 3mm (GPIO23); LED_D3.0mm
D11, D12, D13, D14, D31, D32: 1N4148; D_DO-35_SOD27_P2.54mm_Vertical_KathodeUp
D23, D24: 1N5819; D_DO-41_SOD81_P3.81mm_Vertical_KathodeUp
F1: PTC 2A 30V+ (RXEF200); Fuse_Bourns_MF-RHT200
H1, H2, H3, H4, H5, H6: M2.5; MountingHole_2.7mm_M2.5
J1: RPi 40-pin socket; PinSocket_2x20_P2.54mm_Vertical
J2: 12-24V IN; TerminalBlock_Phoenix_PT-1,5-2-3.5-H_1x02_P3.50mm_Horizontal
J3: INPUTS 1-4, COM; TerminalBlock_Phoenix_PT-1,5-5-3.5-H_1x05_P3.50mm_Horizontal
J4: OUT3 OUT4 V+; TerminalBlock_Phoenix_PT-1,5-3-3.5-H_1x03_P3.50mm_Horizontal
J5: ANALOG 3V3 A0-A3 GND; TerminalBlock_Phoenix_PT-1,5-6-3.5-H_1x06_P3.50mm_Horizontal
J8: RELAY 1: NO COM NC (pin 1 at the bottom); TerminalBlock_Phoenix_PT-1,5-3-3.5-H_1x03_P3.50mm_Horizontal
J9: RELAY 2: NO COM NC (pin 1 at the bottom); TerminalBlock_Phoenix_PT-1,5-3-3.5-H_1x03_P3.50mm_Horizontal
J10: DS3231 module; PinSocket_1x05_P2.54mm_Vertical
J11: ADS1115 module; PinSocket_1x10_P2.54mm_Vertical
K1, K2: SRD-05VDC-SL-C; Relay_SPDT_SANYOU_SRD_Series_Form_C
Q1, Q2: BC337; TO-92_Inline_Wide
Q3, Q4: IRLZ44N; TO-220-3_Vertical
R1, R30, R31, R32, R33, R41, R42: 1k; R_Axial_DIN0207_L6.3mm_D2.5mm_P2.54mm_Vertical
R2: 330; R_Axial_DIN0207_L6.3mm_D2.5mm_P2.54mm_Vertical
R11, R12, R13, R14: 3.3k; R_Axial_DIN0207_L6.3mm_D2.5mm_P2.54mm_Vertical
R15, R16, R17, R18, R50: 10k; R_Axial_DIN0207_L6.3mm_D2.5mm_P2.54mm_Vertical
R23, R24: 100; R_Axial_DIN0207_L6.3mm_D2.5mm_P2.54mm_Vertical
R27, R28: 100k; R_Axial_DIN0207_L6.3mm_D2.5mm_P2.54mm_Vertical
SW1: button 6x6; SW_PUSH_6mm
U1: R-78B5.0-2.0; Converter_DCDC_RECOM_R-78B-2.0_THT
U11, U12, U13, U14: PC817; DIP-4_W7.62mm

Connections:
+3V3: J1.1 (3V3), J1.17 (3V3), J5.1, J10.1, J11.1, R15.1, R16.1, R17.1, R18.1, R50.1
+5V: C3.1, D31.1 (K), D32.1 (K), J1.2 (5V), J1.4 (5V), K1.2, K2.2, R1.1, U1.3 (OUT)
A0_T: J5.2, R30.1
A1_T: J5.3, R31.1
A2_T: J5.4, R32.1
A3_T: J5.5, R33.1
AIN0: J11.7, R30.2
AIN1: J11.8, R31.2
AIN2: J11.9, R32.2
AIN3: J11.10, R33.2
BTN: C50.1, J1.31 (GCLK2/GPIO6), R50.2, SW1.1
COM_IN: D11.2 (A), D12.2 (A), D13.2 (A), D14.2 (A), J3.5, U11.2, U12.2, U13.2, U14.2
GND: C1.2, C3.2, C50.2, D2.2 (A2), D3.1 (K), D4.1 (K), J1.6 (GND), J1.9 (GND), J1.14 (GND), J1.20 (GND), J1.25 (GND), J1.30 (GND), J1.34 (GND), J1.39 (GND), J2.2, J5.6, J10.5, J11.2, J11.5, Q1.3 (E), Q2.3 (E), Q3.3 (S), Q4.3 (S), R27.2, R28.2, SW1.2, U1.2 (GND), U11.3, U12.3, U13.3, U14.3
IN1: J1.11 (GPIO17), R15.2, U11.4
IN1_A: D11.1 (K), R11.2, U11.1
IN1_T: J3.1, R11.1
IN2: J1.13 (GPIO27), R16.2, U12.4
IN2_A: D12.1 (K), R12.2, U12.1
IN2_T: J3.2, R12.1
IN3: J1.15 (GPIO22), R17.2, U13.4
IN3_A: D13.1 (K), R13.2, U13.1
IN3_T: J3.3, R13.1
IN4: J1.29 (GCLK1/GPIO5), R18.2, U14.4
IN4_A: D14.1 (K), R14.2, U14.1
IN4_T: J3.4, R14.1
K1_B: Q1.2 (B), R41.2
K1_C: D31.2 (A), K1.5, Q1.1 (C)
K1_COM: J8.2, K1.1
K1_NC: J8.3, K1.4
K1_NO: J8.1, K1.3
K2_B: Q2.2 (B), R42.2
K2_C: D32.2 (A), K2.5, Q2.1 (C)
K2_COM: J9.2, K2.1
K2_NC: J9.3, K2.4
K2_NO: J9.1, K2.3
LED_ST: J1.16 (GPIO23), R2.1
OUT1: J1.18 (GPIO24), R41.1
OUT2: J1.22 (GPIO25), R42.1
OUT3: J1.32 (PWM0/GPIO12), R23.1
OUT3_D: D23.2 (A), J4.1, Q3.2 (D)
OUT3_G: Q3.1 (G), R23.2, R27.1
OUT4: J1.36 (GPIO16), R24.1
OUT4_D: D24.2 (A), J4.2, Q4.2 (D)
OUT4_G: Q4.1 (G), R24.2, R28.1
PWR_LED: D3.2 (A), R1.2
SCL: J1.5 (SCL/GPIO3), J10.3, J11.3
SDA: J1.3 (SDA/GPIO2), J10.2, J11.4
ST_LED: D4.2 (A), R2.2
VIN: C1.1, D1.1 (K), D2.1 (A1), D23.1 (K), D24.1 (K), J4.3, U1.1 (IN)
VIN_F: D1.2 (A), F1.2
VIN_RAW: F1.1, J2.1

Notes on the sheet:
Raspberry Pi header (HAT socket, bottom side)
Power: 12-24 V in, 5 V / 2 A module to the Pi (pins 2+4)
4 isolated inputs (PC817): 5-24 V between INx and COM -> GPIO low
2 relays K1/K2 (GPIO24/25), 5 V coils, contacts max 24 V / 5 A
2 outputs (GPIO12/16): low-side MOSFET, load between V+ and OUTx
Plug-in modules: ADS1115 (0x48, analog 0-3.3 V), DS3231 clock (0x68); button GPIO6
Mounting holes
RoboOS IoT shield THT v0.1 - FIRST DRAFT, not built or tested. Through-hole parts only.
GPIO: IN1-4 = GPIO17/27/22/5 (low = input on), relays K1/K2 = GPIO24/25, MOSFETs = GPIO12/16,
status LED GPIO23, button GPIO6 (low = pressed), I2C GPIO2/3: ADS1115 module 0x48, DS3231 module 0x68.
5 V goes to the Pi pins 2/4: do not power the Pi from its USB port at the same time. Max input 28 V.
Relay contacts: low voltage only (max 24 V, 5 A) - not for 230 V.

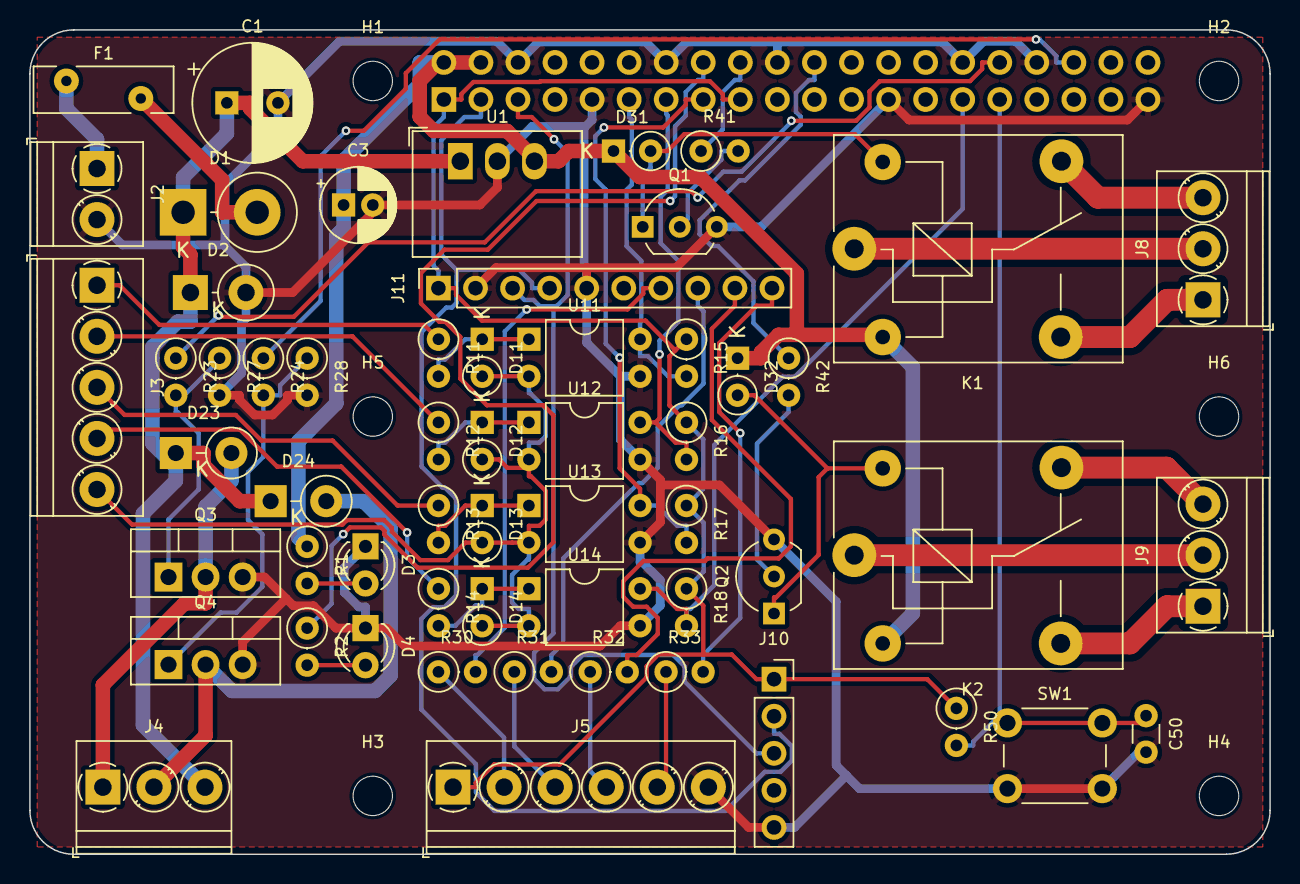
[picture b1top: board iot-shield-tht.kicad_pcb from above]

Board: 2 copper layers, 85.0 x 56.5 mm, 64 parts (1 on the bottom side), 51 nets.

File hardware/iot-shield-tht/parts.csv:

Qty,Value,Refs,Footprint,Note
1,100u 50V,C1,CP_Radial_D8.0mm_P3.50mm,
1,47u 16V,C3,CP_Radial_D5.0mm_P2.00mm,
1,100n,C50,C_Disc_D3.0mm_W1.6mm_P2.50mm,
1,1N5822,D1,D_DO-201AD_P5.08mm_Vertical_KathodeUp,"reverse polarity protection, Schottky 3 A 40 V, standing"
1,P6KE30CA,D2,D_DO-15_P3.81mm_Vertical_KathodeUp,"bidirectional TVS 600 W, standoff 25.6 V"
1,red 3mm (power),D3,LED_D3.0mm,
1,green 3mm (GPIO23),D4,LED_D3.0mm,
6,1N4148,D11 D12 D13 D14 D31 D32,D_DO-35_SOD27_P2.54mm_Vertical_KathodeUp,
2,1N5819,D23 D24,D_DO-41_SOD81_P3.81mm_Vertical_KathodeUp,
1,PTC 2A 30V+ (RXEF200),F1,Fuse_Bourns_MF-RHT200,"radial PTC, 5.1 mm lead spacing, hold 2 A, >= 30 V (Littelfuse RXEF200, Bourns MF-R200)"
1,RPi 40-pin socket,J1,PinSocket_2x20_P2.54mm_Vertical,"2x20 female, 8.5 mm (on the bottom side)"
1,12-24V IN,J2,"TerminalBlock_Phoenix_PT-1,5-2-3.5-H_1x02_P3.50mm_Horizontal",
1,"INPUTS 1-4, COM",J3,"TerminalBlock_Phoenix_PT-1,5-5-3.5-H_1x05_P3.50mm_Horizontal",
1,OUT3 OUT4 V+,J4,"TerminalBlock_Phoenix_PT-1,5-3-3.5-H_1x03_P3.50mm_Horizontal",
1,ANALOG 3V3 A0-A3 GND,J5,"TerminalBlock_Phoenix_PT-1,5-6-3.5-H_1x06_P3.50mm_Horizontal",
1,RELAY 1: NO COM NC (pin 1 at the bottom),J8,"TerminalBlock_Phoenix_PT-1,5-3-3.5-H_1x03_P3.50mm_Horizontal",
1,RELAY 2: NO COM NC (pin 1 at the bottom),J9,"TerminalBlock_Phoenix_PT-1,5-3-3.5-H_1x03_P3.50mm_Horizontal",
1,DS3231 module,J10,PinSocket_1x05_P2.54mm_Vertical,"the small DS3231 'RTC for Raspberry Pi' board: + D C NC - (address 0x68, CR1220 on the module)"
1,ADS1115 module,J11,PinSocket_1x10_P2.54mm_Vertical,the common blue ADS1115 board: VDD GND SCL SDA ADDR ALRT A0 A1 A2 A3 (ADDR = GND -> 0x48)
2,SRD-05VDC-SL-C,K1 K2,Relay_SPDT_SANYOU_SRD_Series_Form_C,"5 V coil ~70 mA, contacts 10 A - here max 24 V / 5 A (terminal block, tracks)"
2,BC337,Q1 Q2,TO-92_Inline_Wide,
2,IRLZ44N,Q3 Q4,TO-220-3_Vertical,"logic-level N-MOSFET (IRLZ44N, IRLB8721, IRL540N)"
7,1k,R1 R30 R31 R32 R33 R41 R42,R_Axial_DIN0207_L6.3mm_D2.5mm_P2.54mm_Vertical,
1,330,R2,R_Axial_DIN0207_L6.3mm_D2.5mm_P2.54mm_Vertical,
4,3.3k,R11 R12 R13 R14,R_Axial_DIN0207_L6.3mm_D2.5mm_P2.54mm_Vertical,
5,10k,R15 R16 R17 R18 R50,R_Axial_DIN0207_L6.3mm_D2.5mm_P2.54mm_Vertical,
2,100,R23 R24,R_Axial_DIN0207_L6.3mm_D2.5mm_P2.54mm_Vertical,
2,100k,R27 R28,R_Axial_DIN0207_L6.3mm_D2.5mm_P2.54mm_Vertical,
1,button 6x6,SW1,SW_PUSH_6mm,
1,R-78B5.0-2.0,U1,Converter_DCDC_RECOM_R-78B-2.0_THT,"5 V 2 A switching 78xx replacement (RECOM R-78B5.0-2.0, TRACO TSR 2-2450, Mornsun K7805-2000R3)"
4,PC817,U11 U12 U13 U14,DIP-4_W7.62mm,

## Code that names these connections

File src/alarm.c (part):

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        b[n] = 0;
        char e[80];
        lock(); parse(b, 0, e, sizeof(e)); unlock();
        kprintf("IoT shield: IN1 GPIO17 door (delay), IN2 GPIO27 window, IN3 GPIO22 PIR (interior, normally open),\n"
                "IN4 GPIO5 tamper (24h); siren = relay K1 / OUT1 GPIO24, LED GPIO23. Rename / remove with 'alarm zone'.\n");
        changed = 1;
    } else if (!strcmp(a, "remote") && argc > 2) {
        scopy(remote, !strcmp(argv[2], "off") || !strcmp(argv[2], "none") ? "" : argv[2], sizeof(remote));
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
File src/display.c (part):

/*
 * display.c - small I2C displays on GPIO2/3 (the same bus as the sensors):
 *   OLED 128x64 / 128x32 with an SSD1306 or SH1106 controller at 0x3C / 0x3D (text in the 8x16 font:
 *        16 columns x 4 rows, or 2 rows on 128x32),
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static u8 st_byte;                              /* OLED status byte read at detection (SSD1306 vs SH1106) */
static char txt[MAXR][MAXC + 1], sent[MAXR][MAXC + 1];
static int ok, busy, noack;                    /* noack: the display never ACKs - bit-banged writes */
static int spi_bus, cfg_spi;                   /* 0.72: SH1106 on SPI0 = Waveshare 1.3" OLED HAT (DC GPIO24, RST GPIO25) */
#define HAT_DC  24
#define HAT_RST 25
/* every OLED write starts with the I2C control byte (0x00 commands / 0x40 data): on SPI it becomes the DC pin */
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}

int display_found(void) { return ok; }
int display_hat(void) { return cfg_spi; }         /* 0.136: the Waveshare HAT (its joystick uses GPIO5/6/13/19/26) */
int display_rows(void) { return ok ? rows : 0; }
int display_cols(void) { return ok ? cols : 0; }

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    else if (!strcmp(a, "hat")) {                /* Waveshare 1.3" OLED HAT: SH1106 on SPI + keys */
        cfg_spi = 1; cfg_type = D_SH1106; cfg_h = 64; save_cfg();
        busy = 1; detect(); busy = 0; restart();
        kprintf("Waveshare 1.3\" OLED HAT: SH1106 on SPI0 (CE0, DC GPIO24, RST GPIO25), keys on GPIO21/20/16,\n"
                "joystick GPIO6/19/5/26/13. KEY1 = next screen; on 'display radio': KEY2/KEY3 seek, left/right tune,\n"
                "up/down volume, press on/off. 'display type auto' goes back to I2C displays.\n");
    }
    else if (!strcmp(a, "keys")) {
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

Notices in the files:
README.md:
`lwip/` | lwIP 2.2.1 TCP/IP stack (unmodified, BSD license)
- TCP/IP: lwIP by Adam Dunkels and the lwIP developers (BSD license, `lwip/COPYING`).
- Pictures: stb_image by Sean Barrett (public domain / MIT, `third_party/stb_image.h`).
